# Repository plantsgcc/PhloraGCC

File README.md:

# PhobGCCv2-HW
Seperate repository for the hardware used in the PhobGCC v2.0

The PhobGCC v2.0 board is licensed under CERN Open Hardware Licence Version 2 - Strongly Reciprocal.
This means that any changes made to the board should be made public and CHANGES.txt be updated to reflect said changes.

--

PhloraGCC v2.0.2

-aesthetic changes 

-left z + routing to RP2040 directly

-repositioned L and R through holes for easier alignment, especially with JST 2 pin headers

-USB-C in place of Micro USB for flashing

-changed start pad shape to emulate d-pad, expanded D-Pad + Start pads a smidge

-thru-holes on ABXY pads for easy installation and implementation of Tactile Push Button switch usage (6x6mm form factor)

-integration of experimental Phob 2.0.3 ESD protection circuit; 47uF Polarized Capacitor, 30v 1a Schottky Diode, Unidirectional Zener Diode

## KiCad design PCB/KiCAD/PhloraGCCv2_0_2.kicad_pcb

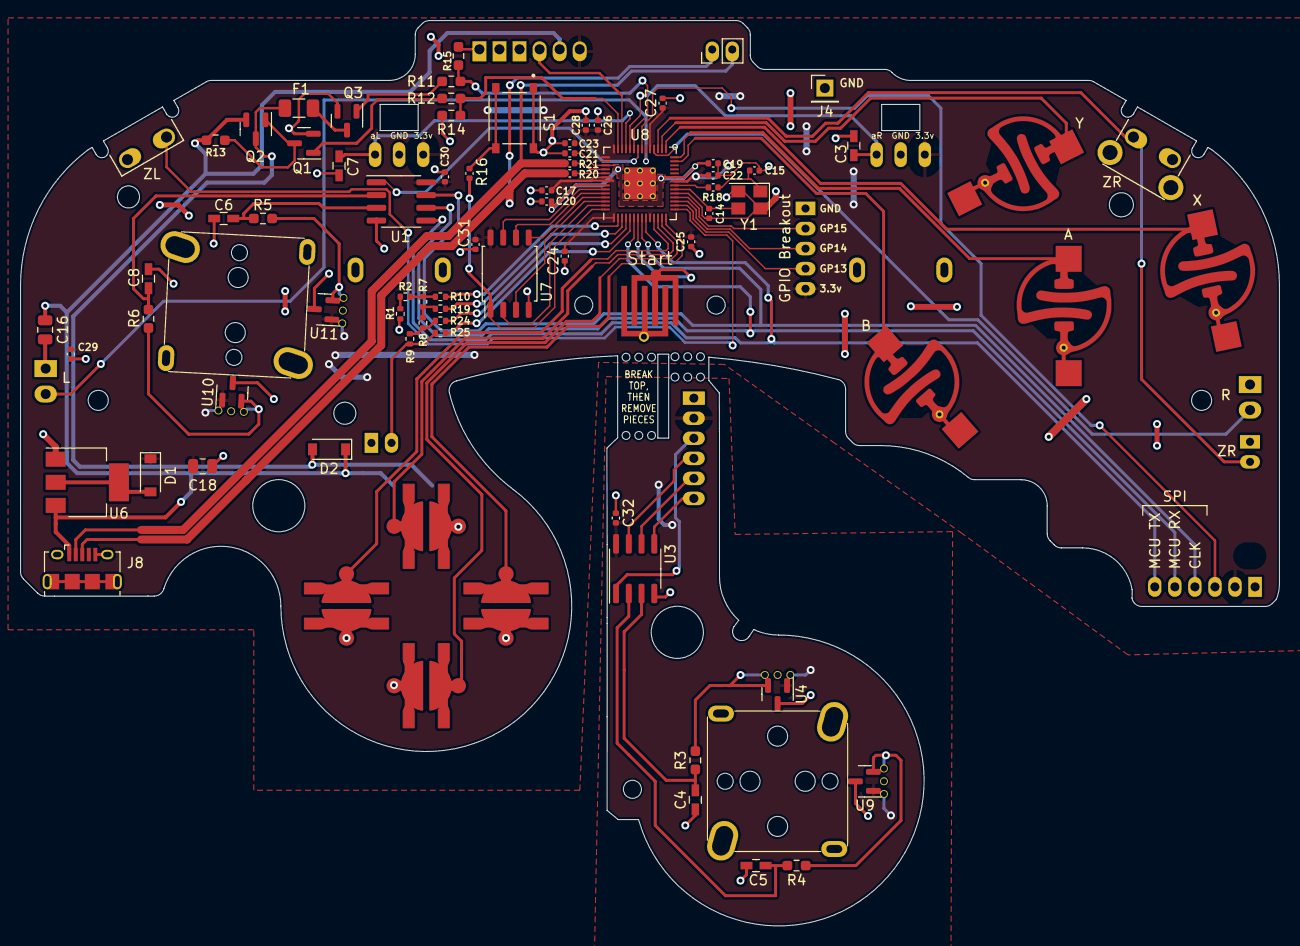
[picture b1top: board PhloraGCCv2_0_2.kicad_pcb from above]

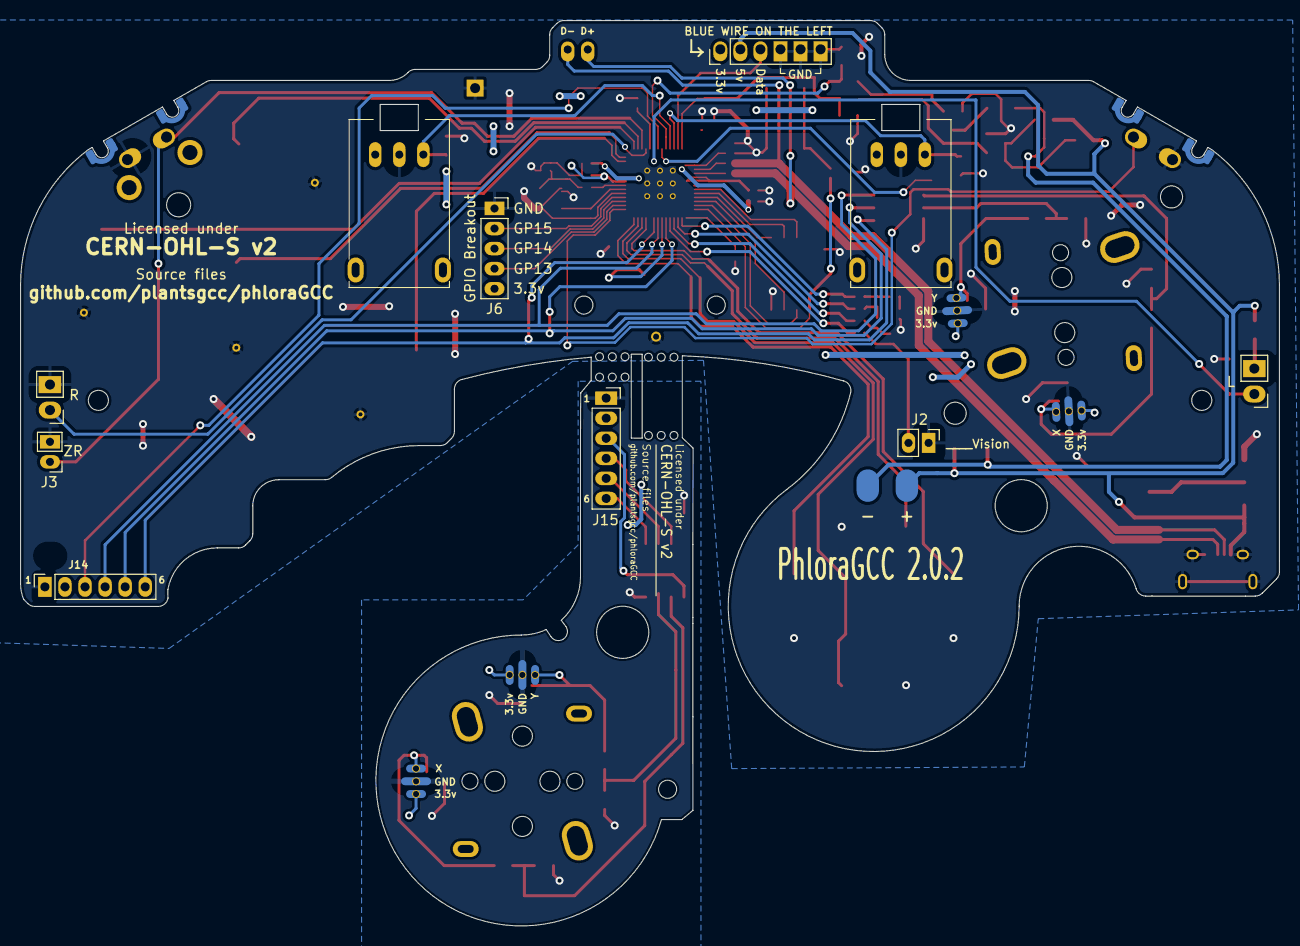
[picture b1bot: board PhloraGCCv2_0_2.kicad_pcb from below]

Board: 2 copper layers, 125.5 x 90.3 mm, 106 parts (11 on the bottom side), 73 nets.

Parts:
C3, C4, C5, C6, C7, C8: 0.047u; C_0603_HandSoldering
C14, C15: 27p; C_0402_1005Metric
C16, C18: 10u; C_0805_2012Metric
C17, C19, C20, C22, C24, C25, C26, C27, C28, C29, C30, C31, C32: 100n; C_0402_1005Metric
C21, C23: 1u; C_0402_1005Metric
D1: MBR0520; D_SOD-123
D2: M7C; D_SOD-123
F1: Fuse; Fuse_1206_3216Metric
H1: 5.2mm; MountingHole_5.2mm
H2: Slot
H3, H4: 2mm; MountingHole_2.0mm
H5, H6: 1.8mm; MountingHole_1.8mm
H7: 2.4mm; MountingHole_2.4mm
H8, H9: 2.2mm; MountingHole_2.2mm
H10: MountingHole; MountingHole_1.8mm
H11: MountingHole; MountingHole_5.2mm
H12, H13: MountingHole; MountingHole_2.0mm
H14: MouseBite; breakaway-mousebites-double-v2-small
H15: MouseBite; breakaway-mousebites-double-v2-large
J1: Conn_01x06_Female; GCC_Header_Straight_1x06_Pitch2.00mm
J2, J11: Conn_01x02; PinHeader_1x02_P2.00mm_Vertical
J3: Conn_01x02; PinHeader_1x02_P2.00mm_Horizontal
J4: Conn_01x01; PinHeader_1x01_P2.54mm_Vertical
J5: Rumble; rumble_pins
J6, J14, J15: Conn_01x06; PinSocket_1x06_P2.00mm_Vertical
J8: USB_B_Micro; USB_Micro-B_Amphenol_10118194_Horizontal
Q1, Q3: Q_NMOS_GSD; SOT-23
Q2: Q_PMOS_GDS; SOT-23
R1, R2, R7, R8, R9: 180; R_0402_1005Metric
R3, R4, R5, R6: 2k; R_0603_1608Metric_Pad0.98x0.95mm_HandSolder
R10, R19, R24, R25: 316; R_0402_1005Metric
R11, R12: 100R; R_0603_1608Metric_Pad0.98x0.95mm_HandSolder
R13, R14, R15: 10k; R_0603_1608Metric_Pad0.98x0.95mm_HandSolder
R16, R18: 1k; C_0402_1005Metric
R20, R21: 27; C_0402_1005Metric
RV1, RV2: R_POT_MountingPin; GCC_Slider
S1: BOOTSEL; SW_TS-1187A-B-A-B
SW1: A; ABXY_Contact_Omron_Switch
SW2: B; ABXY_Contact_Omron_Switch
SW3: X; ABXY_Contact_Omron_Switch
SW4: Y; ABXY_Contact_Omron_Switch
SW5: Start; Start_Contact
SW6: L; Pin_Header_Straight_1x02_Pitch2.54mm
SW7: R; Pin_Header_Straight_1x02_Pitch2.54mm
SW8: Z; Z_Switch_Edge_Omron
SW8L: ZL; Z_Switch_Edge_Omron
SW9: Dleft; Dpad_Contact_TL3315NF_2
SW10: Dup; Dpad_Contact_TL3315NF_2
SW11: Dright; Dpad_Contact_TL3315NF_2
SW12: Ddown; Dpad_Contact_TL3315NF_2
U1, U3: MCP3002; SOIC-8_3.9x4.9mm_P1.27mm
U2: Stickbox_Assembly_Main; GCC_Stickbox_Hall_Only
U4, U9, U10, U11: DRV5055A2xDBZxQ1; SOT-23
U5: Stickbox_Assembly_CStick; GCC_Stickbox_Hall_Only
U6: AMS1117-3.3; SOT-223-3_TabPin2
U7: W25Q128JVS; SOIC-8_5.23x5.23mm_P1.27mm
U8: RP2040; RP2040-QFN-56
Y1: Crystal_GND24; Crystal_SMD_3225-4Pin_3.2x2.5mm

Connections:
+1V1: C19.1, C20.1, C21.1, U8.23 (DVDD), U8.45 (VREG_VOUT), U8.50 (DVDD)
+3V3: C17.1, C18.1, C22.1, C23.1, C24.1, C25.1, C26.1, C27.1, C28.1, C29.1, C30.1, C31.1, D1.1 (K), J1.1, J6.2, J14.2, RV1.1 (V+), RV2.1 (V+), U1.8 (VDD/VREF), U2.1 (H1XV), U2.4 (H1YV), U7.8 (VCC), U8.1 (IOVDD), U8.10 (IOVDD), U8.22 (IOVDD), U8.33 (IOVDD), U8.42 (IOVDD), U8.43 (ADC_AVDD), U8.44 (VREG_IN), U8.48 (USB_VDD), U8.49 (IOVDD), U10.1 (VCC), U11.1 (VCC)
+5V: C16.1, D2.1 (K), J1.2, J5.1, J8.1 (VBUS), Q2.2 (S), R13.2, U6.3 (VI)
/A: SW1.1, U8.28 (GPIO17)
/B: SW2.1, U8.27 (GPIO16)
/Brake: R12.1, R14.2, U8.41 (GPIO29_ADC3)
/CLK: J14.4, U1.7 (CLK), U8.8 (GPIO6)
/CLK2: J15.4, U3.7 (CLK)
/CS1: U1.1 (~CS/SHDN), U8.36 (GPIO24)
/CS2: J14.3, U8.35 (GPIO23)
/CS2_2: J15.3, U3.1 (~CS/SHDN)
/C_x_filt: C5.1, R4.1, U3.2 (CH0)
/C_y_filt: C4.1, R3.1, U3.3 (CH1)
/Ddown: SW12.1, U8.13 (GPIO10)
/Din: J14.6, U1.5 (DIN), U8.9 (GPIO7)
/Din2: J15.6, U3.5 (DIN)
/Dleft: SW9.1, U8.11 (GPIO8)
/Dout: J14.5, U1.6 (DOUT), U8.6 (GPIO4)
/Dout2: J15.5, U3.6 (DOUT)
/Dright: SW11.1, U8.14 (GPIO11)
/Dup: SW10.1, U8.12 (GPIO9)
/GCC_DATA: J1.3, U8.40 (GPIO28_ADC2)
/GND_C: C4.2, C5.2, C32.2, J15.1, U3.4 (VSS), U4.3 (GND), U5.2 (H1XG), U5.5 (H1YG), U9.3 (GND)
/GPIO12: SW8L.2, U8.15 (GPIO12)
/GPIO13: J6.3, U8.16 (GPIO13)
/GPIO14: J6.4, U8.17 (GPIO14)
/GPIO15: J6.5, U8.18 (GPIO15)
/H1XS: R6.2, U2.3 (H1XS), U10.2 (OUT)
/H1YS: R5.2, U2.6 (H1YS), U11.2 (OUT)
/H2XS: R4.2, U5.3 (H1XS), U9.2 (OUT)
/H2YS: R3.2, U4.2 (OUT), U5.6 (H1YS)
/L: SW6.1, U8.34 (GPIO22)
/Ladder1: R10.2, U8.2 (GPIO0)
/Ladder2: R19.2, U8.3 (GPIO1)
/Ladder3: R24.2, U8.4 (GPIO2)
/Ladder4: R25.2, U8.5 (GPIO3)
/Lanalog: C7.1, RV1.3 (Signal), U8.39 (GPIO27_ADC1)
/QSPI_SCLK: U7.6 (CLK), U8.52 (QSPI_SCLK)
/QSPI_SD0: U7.5 (DI(IO0)), U8.53 (QSPI_SD0)
/QSPI_SD1: U7.2 (DO(IO1)), U8.55 (QSPI_SD1)
/QSPI_SD2: U7.3 (IO2), U8.54 (QSPI_SD2)
/QSPI_SD3: U7.7 (IO3), U8.51 (QSPI_SD3)
/QSPI_SS: R16.1, U7.1 (~CS), U8.56 (QSPI_SS)
/R: SW7.1, U8.32 (GPIO21)
/Ranalog: C3.1, RV2.3 (Signal), U8.38 (GPIO26_ADC0)
/Rumble: R11.1, R15.2, U8.37 (GPIO25)
/Start: SW5.1, U8.7 (GPIO5)
/Stick_x_filt: C8.1, R6.1, U1.2 (CH0)
/Stick_y_filt: C6.1, R5.1, U1.3 (CH1)
/USB_D+: J8.3 (D+), J11.1, R20.1
/USB_D-: J8.2 (D-), J11.2, R21.1
/V: J2.2, R9.1, R25.1
/X: SW3.1, U8.29 (GPIO18)
/XIN: C14.1, U8.20 (XIN), Y1.3
/XOUT: R18.1, U8.21 (XOUT)
/Y: SW4.1, U8.30 (GPIO19)
/Z: J3.2, SW8.1, U8.31 (GPIO20)
/~USB_BOOT: R16.2, S1.C, S1.D
GND: C3.2, C6.2, C7.2, C8.2, C14.2, C15.2, C16.2, C17.2, C18.2, C19.2, C20.2, C21.2, C22.2, C23.2, C24.2, C25.2, C26.2, C27.2, C28.2, C29.2, C30.2, C31.2, J1.4, J1.5, J1.6, J2.1, J3.1, J4.1, J6.6, J8.5 (GND), J8.6 (Shield), J14.1, Q1.2 (S), Q3.2 (S), R1.2, R14.1, R15.1, RV1.2 (GND), RV2.2 (GND), S1.A, S1.B, SW1.2, SW2.2, SW3.2, SW4.2, SW5.2, SW6.2, SW7.2, SW8.2, SW8L.1, SW9.2, SW10.2, SW11.2, SW12.2, U1.4 (VSS), U2.2 (H1XG), U2.5 (H1YG), U6.1 (GND), U7.4 (GND), U8.19 (TESTEN), U8.57 (GND), U10.3 (GND), U11.3 (GND), Y1.2, Y1.4
unnamed: C15.1, R18.2, Y1.1
unnamed: D1.2 (A), U6.2 (VO)
unnamed: D2.2 (A), F1.1, J5.2, Q2.3 (D)
unnamed: F1.2, Q3.3 (D)
unnamed: Q1.1 (G), R12.2
unnamed: Q1.3 (D), Q2.1 (G), R13.1
unnamed: Q3.1 (G), R11.2
unnamed: R1.1, R2.2
unnamed: R2.1, R7.2, R10.1
unnamed: R7.1, R8.2, R19.1
unnamed: R20.2, U8.47 (USB_DP)
unnamed: R21.2, U8.46 (USB_DM)
unnamed: R8.1, R9.2, R24.1
VCC: C32.1, J15.2, U3.8 (VDD/VREF), U4.1 (VCC), U5.1 (H1XV), U5.4 (H1YV), U9.1 (VCC)

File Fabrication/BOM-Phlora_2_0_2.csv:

Comment,Designator,Footprint,LCSC
27,"R20,R21",C_0402_1005Metric,C102781
316,"R10,R19,R24,R25",R_0402_1005Metric,C103167
1k,"R16,R18",C_0402_1005Metric,C11702
USB_B_Micro,J8,USB_Micro-B_Amphenol_10118194_Horizontal,C132563
Q_PMOS_GDS,Q2,SOT-23,C15127
100n,"C17,C19,C20,C22,C24,C25,C26,C27,C28,C29,C30,C31,C32",C_0402_1005Metric,C1525
27p,"C14,C15",C_0402_1005Metric,C1557
Crystal_GND24,Y1,Crystal_SMD_3225-4Pin_3.2x2.5mm,C156247
10u,"C16,C18",C_0805_2012Metric,C15850
0.047u,"C3,C4,C5,C6,C7,C8",C_0603_HandSoldering,C1622
RP2040,U8,RP2040-QFN-56,C2040
Q_NMOS_GSD,"Q1,Q3",SOT-23,C20917
MCP3002,"U1,U3",SOIC-8_3.9x4.9mm_P1.27mm,C219561
100R,"R11,R12",R_0603_1608Metric_Pad0.98x0.95mm_HandSolder,C22775
2k,"R3,R4,R5,R6",R_0603_1608Metric_Pad0.98x0.95mm_HandSolder,C22975
10k,"R13,R14,R15",R_0603_1608Metric_Pad0.98x0.95mm_HandSolder,C25804
DRV5055A2xDBZxQ1,"U10,U11,U4,U9",SOT-23,C266131
AMS1117-3.3,U6,SOT-223-3_TabPin2,C2909825
BOOTSEL,S1,SW_TS-1187A-B-A-B,C318884
180,"R1,R2,R7,R8,R9",R_0402_1005Metric,C38941
1u,"C21,C23",C_0402_1005Metric,C52923
Fuse,F1,Fuse_1206_3216Metric,C69680
MBR0520,D1,D_SOD-123,C699111
M7C,D2,D_SOD-123,C8598
W25Q128JVS,U7,SOIC-8_5.23x5.23mm_P1.27mm,C97521
A,SW1,ABXY_Contact_Omron_Switch,
B,SW2,ABXY_Contact_Omron_Switch,
Z,SW8,Z_Switch_Edge_Omron,
Dleft,SW9,Dpad_Contact_TL3315NF_2,
Dup,SW10,Dpad_Contact_TL3315NF_2,
Dright,SW11,Dpad_Contact_TL3315NF_2,
Ddown,SW12,Dpad_Contact_TL3315NF_2,
Stickbox_Assembly_Main,U2,GCC_Stickbox_Hall_Only,
Start,SW5,Start_Contact,
Y,SW4,ABXY_Contact_Omron_Switch,
5.2mm,H1,MountingHole_5.2mm,
2mm,H3,MountingHole_2.0mm,
1.8mm,H5,MountingHole_1.8mm,
1.8mm,H6,MountingHole_1.8mm,
2.4mm,H7,MountingHole_2.4mm,
2mm,H4,MountingHole_2.0mm,
2.2mm,H8,MountingHole_2.2mm,
X,SW3,ABXY_Contact_Omron_Switch,
Slot,H2,Slot,
2.2mm,H9,MountingHole_2.2mm,
Conn_01x01,J4,PinHeader_1x01_P2.54mm_Vertical,
MouseBite,H14,breakaway-mousebites-double-v2-small,
Stickbox_Assembly_CStick,U5,GCC_Stickbox_Hall_Only,
MouseBite,H15,breakaway-mousebites-double-v2-large,
MountingHole,H11,MountingHole_5.2mm,
Conn_01x02,J11,PinHeader_1x02_P2.00mm_Vertical,
MountingHole,H13,MountingHole_2.0mm,
MountingHole,H12,MountingHole_2.0mm,
MountingHole,H10,MountingHole_1.8mm,
L,SW6,Pin_Header_Straight_1x02_Pitch2.54mm,
R,SW7,Pin_Header_Straight_1x02_Pitch2.54mm,
R_POT_MountingPin,RV2,GCC_Slider,
R_POT_MountingPin,RV1,GCC_Slider,
Conn_01x06_Female,J1,GCC_Header_Straight_1x06_Pitch2.00mm,
Conn_01x02,J3,PinHeader_1x02_P2.00mm_Horizontal,
Conn_01x06,J6,PinSocket_1x06_P2.00mm_Vertical,
Conn_01x06,J15,PinSocket_1x06_P2.00mm_Vertical,
Rumble,J5,rumble_pins,
Conn_01x06,J14,PinSocket_1x06_P2.00mm_Vertical,
Conn_01x02,J2,PinHeader_1x02_P2.00mm_Vertical,

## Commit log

2022-12-21 Initial PhloraGCC v2.0.2 commit
2022-12-21 File reorganization, fleshing out repository
2023-04-09 push to commit
    committing the push with this commit

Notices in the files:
PCB/KiCAD/PhloraGCCv2_0_2.kicad_pcb:
CERN-OHL-S v2
